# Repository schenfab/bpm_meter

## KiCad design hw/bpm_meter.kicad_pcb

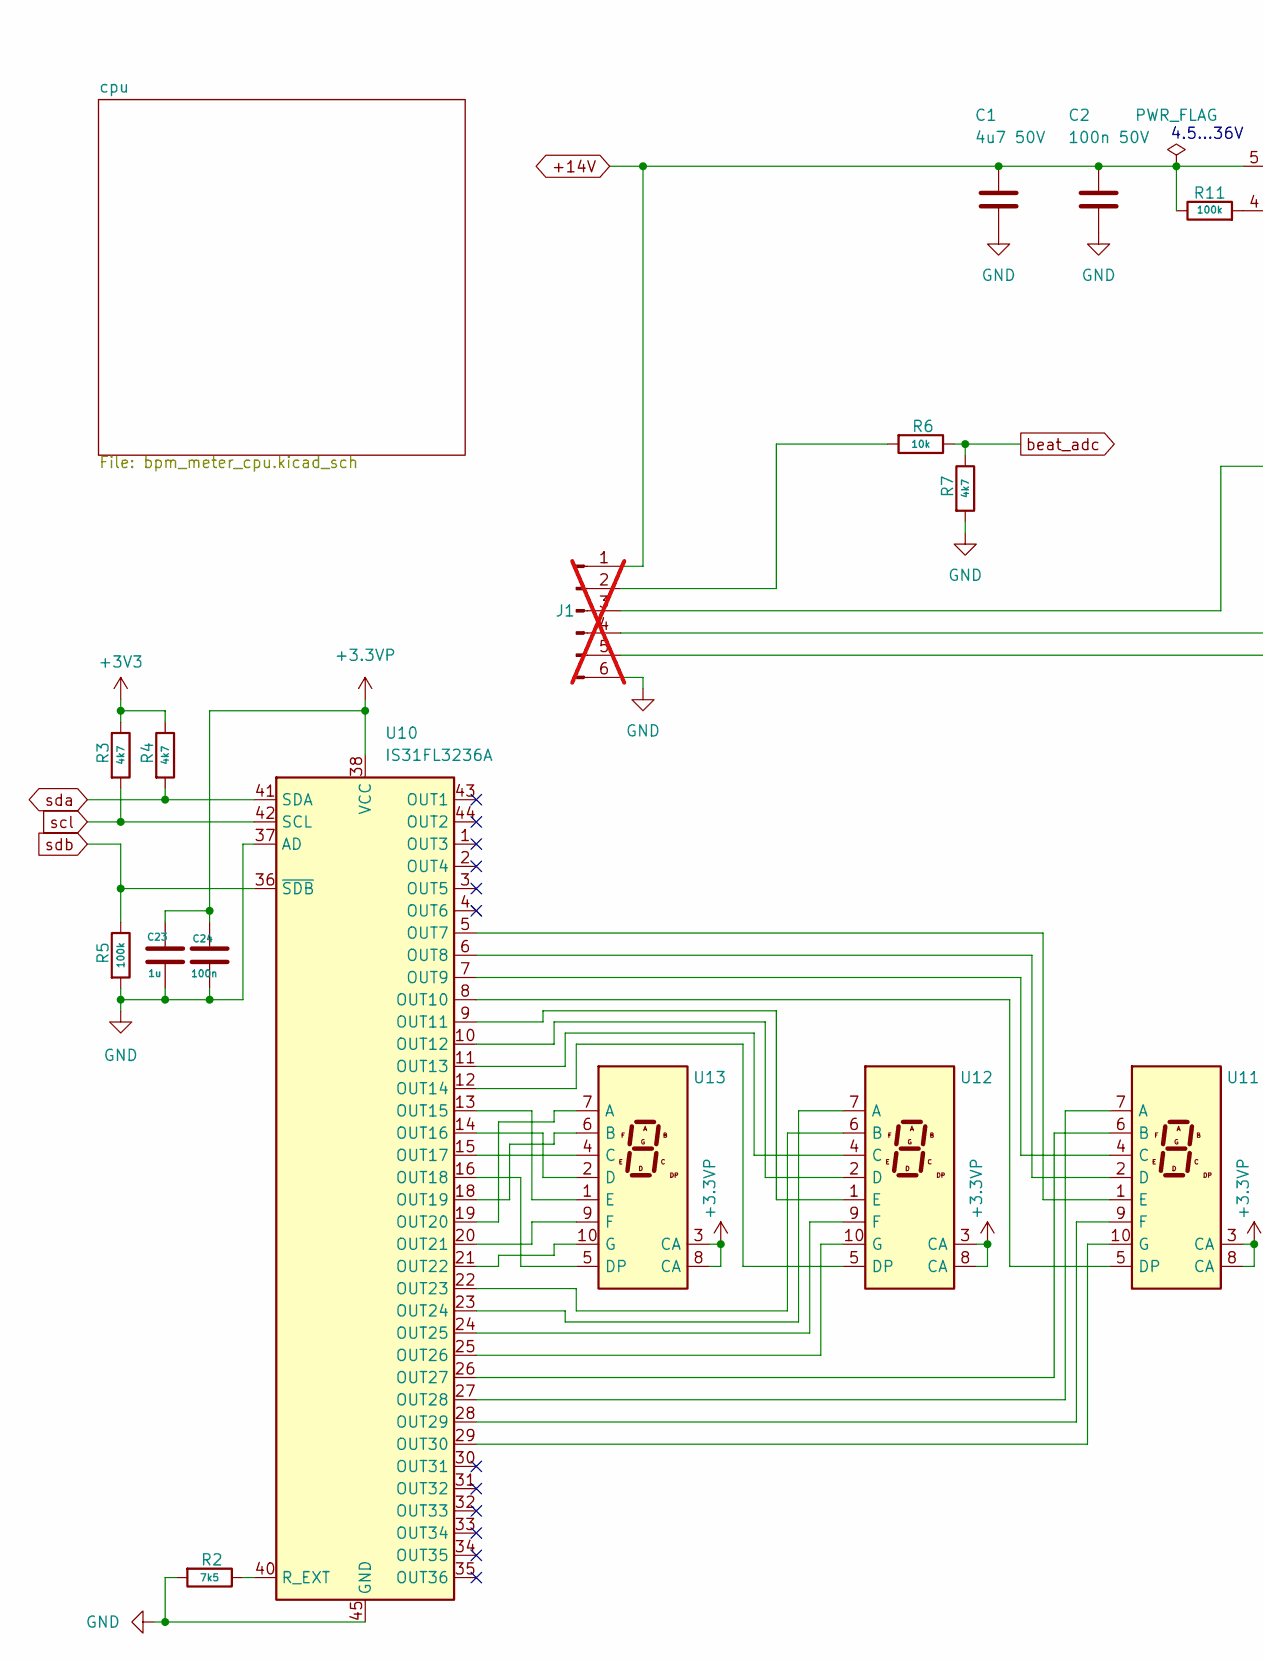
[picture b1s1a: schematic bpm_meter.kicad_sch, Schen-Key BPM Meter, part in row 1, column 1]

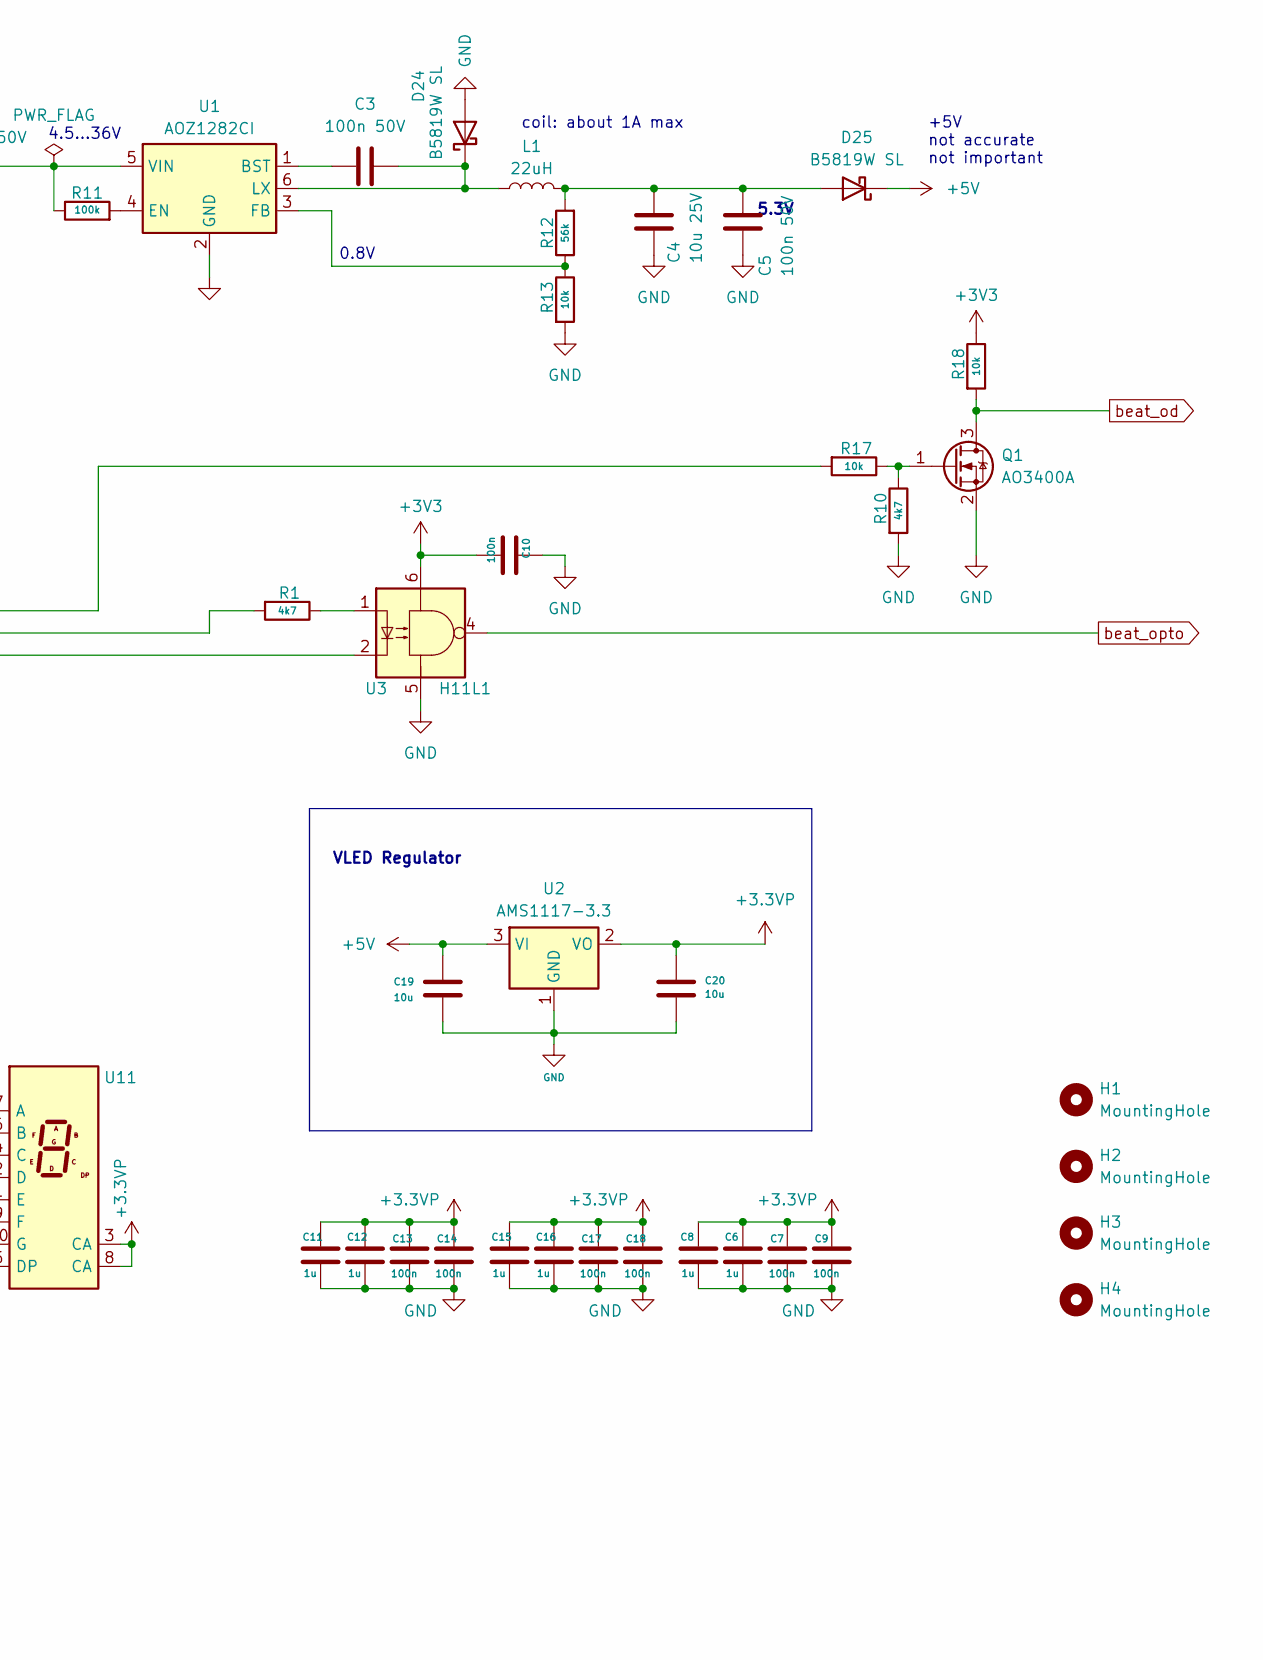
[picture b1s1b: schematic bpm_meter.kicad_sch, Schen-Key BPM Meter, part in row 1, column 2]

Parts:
C1: 4u7 50V; C_1210_3225Metric; JLC C515689
C2, C3, C5: 100n 50V; D_0805_2012Metric; JLC C49678
C4: 10u 25V; D_0805_2012Metric; JLC C15850
C6, C8, C11, C12, C15, C16, C23: 1u; C_0402_1005Metric_Pad0.74x0.62mm_HandSolder
C7, C9, C10, C13, C14, C17, C18, C24: 100n; C_0402_1005Metric_Pad0.74x0.62mm_HandSolder
C19, C20: 10u; C_0603_1608Metric
D24, D25: B5819W SL; D_SOD-123; JLC C8598
H1, H2, H3, H4: MountingHole; MountingHole_2.7mm_M2.5
J1: Conn_01x06_Pin; PinHeader_1x06_P2.54mm_Vertical; not fitted
L1: 22uH; L_MODBUS; JLC C5289423
Q1: AO3400A; SOT-23; JLC C20917
R1, R3, R4, R7, R10: 4k7; R_0402_1005Metric_Pad0.72x0.64mm_HandSolder
R2: 7k5; R_0402_1005Metric_Pad0.72x0.64mm_HandSolder
R5, R11: 100k; R_0402_1005Metric_Pad0.72x0.64mm_HandSolder
R6, R13, R17, R18: 10k; R_0402_1005Metric_Pad0.72x0.64mm_HandSolder
R12: 56k; R_0402_1005Metric_Pad0.72x0.64mm_HandSolder
U1: AOZ1282CI; SOT-23-6; JLC C111916
U2: AMS1117-3.3; SOT-223-3_TabPin2; JLC C6186
U3: H11L1; SOP-6-2.54mm; JLC C78589
U10: IS31FL3236A; QFN-44-5x5mm_P0.4mm; JLC C246443
U11, U12, U13: SLS0391FR1A1GD; SLS0391; JLC C2913076

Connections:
+3.3VP: C6.1, C7.1, C8.1, C9.1, C11.1, C12.1, C13.1, C14.1, C15.1, C16.1, C17.1, C18.1, C20.1, C23.1, C24.1, U2.2 (VO), U10.38 (VCC), U11.3 (CA), U11.8 (CA), U12.3 (CA), U12.8 (CA), U13.3 (CA), U13.8 (CA)
+3V3: C10.2, R3.1, R4.1, R18.1, U3.6; also elsewhere on the board
+5V: C19.1, D25.1 (K), U2.3 (VI); also elsewhere on the board
+14V: C1.1, C2.1, J1.1, R11.1, U1.5 (VIN)
GND: C1.2, C2.2, C4.1, C5.1, C6.2, C7.2, C8.2, C9.2, C10.1, C11.2, C12.2, C13.2, C14.2, C15.2, C16.2, C17.2, C18.2, C19.2, C20.2, C23.2, C24.2, D24.2 (A), J1.6, Q1.2 (S), R2.2, R5.2, R7.2, R10.2, R13.2, U1.2 (GND), U2.1 (GND), U3.5, U10.17 (GND), U10.37 (AD), U10.39 (GND), U10.45 (GND); also elsewhere on the board
unnamed: C3.2, D24.1 (K), L1.1, U1.6 (LX)
unnamed: C4.2, C5.2, D25.2 (A), L1.2, R12.2
unnamed: J1.2, R6.2
unnamed: J1.3, R17.2
unnamed: J1.4, R1.2
unnamed: J1.5, U3.2
unnamed: Q1.1 (G), R10.1, R17.1
unnamed: R1.1, U3.1
unnamed: C3.1, U1.1 (BST)
unnamed: R11.2, U1.4 (EN)
unnamed: R12.1, R13.1, U1.3 (FB)
unnamed: U10.5 (OUT7), U11.1 (E)
unnamed: U10.6 (OUT8), U11.2 (D)
unnamed: U10.7 (OUT9), U11.4 (C)
unnamed: U10.8 (OUT10), U11.5 (DP)
unnamed: U10.9 (OUT11), U12.1 (E)
unnamed: U10.10 (OUT12), U12.2 (D)
unnamed: U10.11 (OUT13), U12.4 (C)
unnamed: U10.12 (OUT14), U12.5 (DP)
unnamed: U10.13 (OUT15), U13.1 (E)
unnamed: U10.14 (OUT16), U13.2 (D)
unnamed: U10.15 (OUT17), U13.4 (C)
unnamed: U10.16 (OUT18), U13.5 (DP)
unnamed: U10.18 (OUT19), U13.6 (B)
unnamed: U10.19 (OUT20), U13.7 (A)
unnamed: U10.20 (OUT21), U13.9 (F)
unnamed: U10.21 (OUT22), U13.10 (G)
unnamed: U10.22 (OUT23), U12.6 (B)
unnamed: U10.23 (OUT24), U12.7 (A)
unnamed: U10.24 (OUT25), U12.9 (F)
unnamed: U10.25 (OUT26), U12.10 (G)
unnamed: U10.26 (OUT27), U11.6 (B)
unnamed: U10.27 (OUT28), U11.7 (A)
unnamed: U10.28 (OUT29), U11.9 (F)
unnamed: U10.29 (OUT30), U11.10 (G)
unnamed: R2.1, U10.40 (R_EXT)
beat_adc: R6.1, R7.1; also elsewhere on the board
beat_od: Q1.3 (D), R18.2; also elsewhere on the board
beat_opto: U3.4; also elsewhere on the board
scl: R3.2, U10.42 (SCL); also elsewhere on the board
sda: R4.2, U10.41 (SDA); also elsewhere on the board
sdb: R5.1, U10.36 (~SDB); also elsewhere on the board

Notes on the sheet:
+5V not accurate not important
coil: about 1A max
5.3V
VLED Regulator
4.5...36V
0.8V

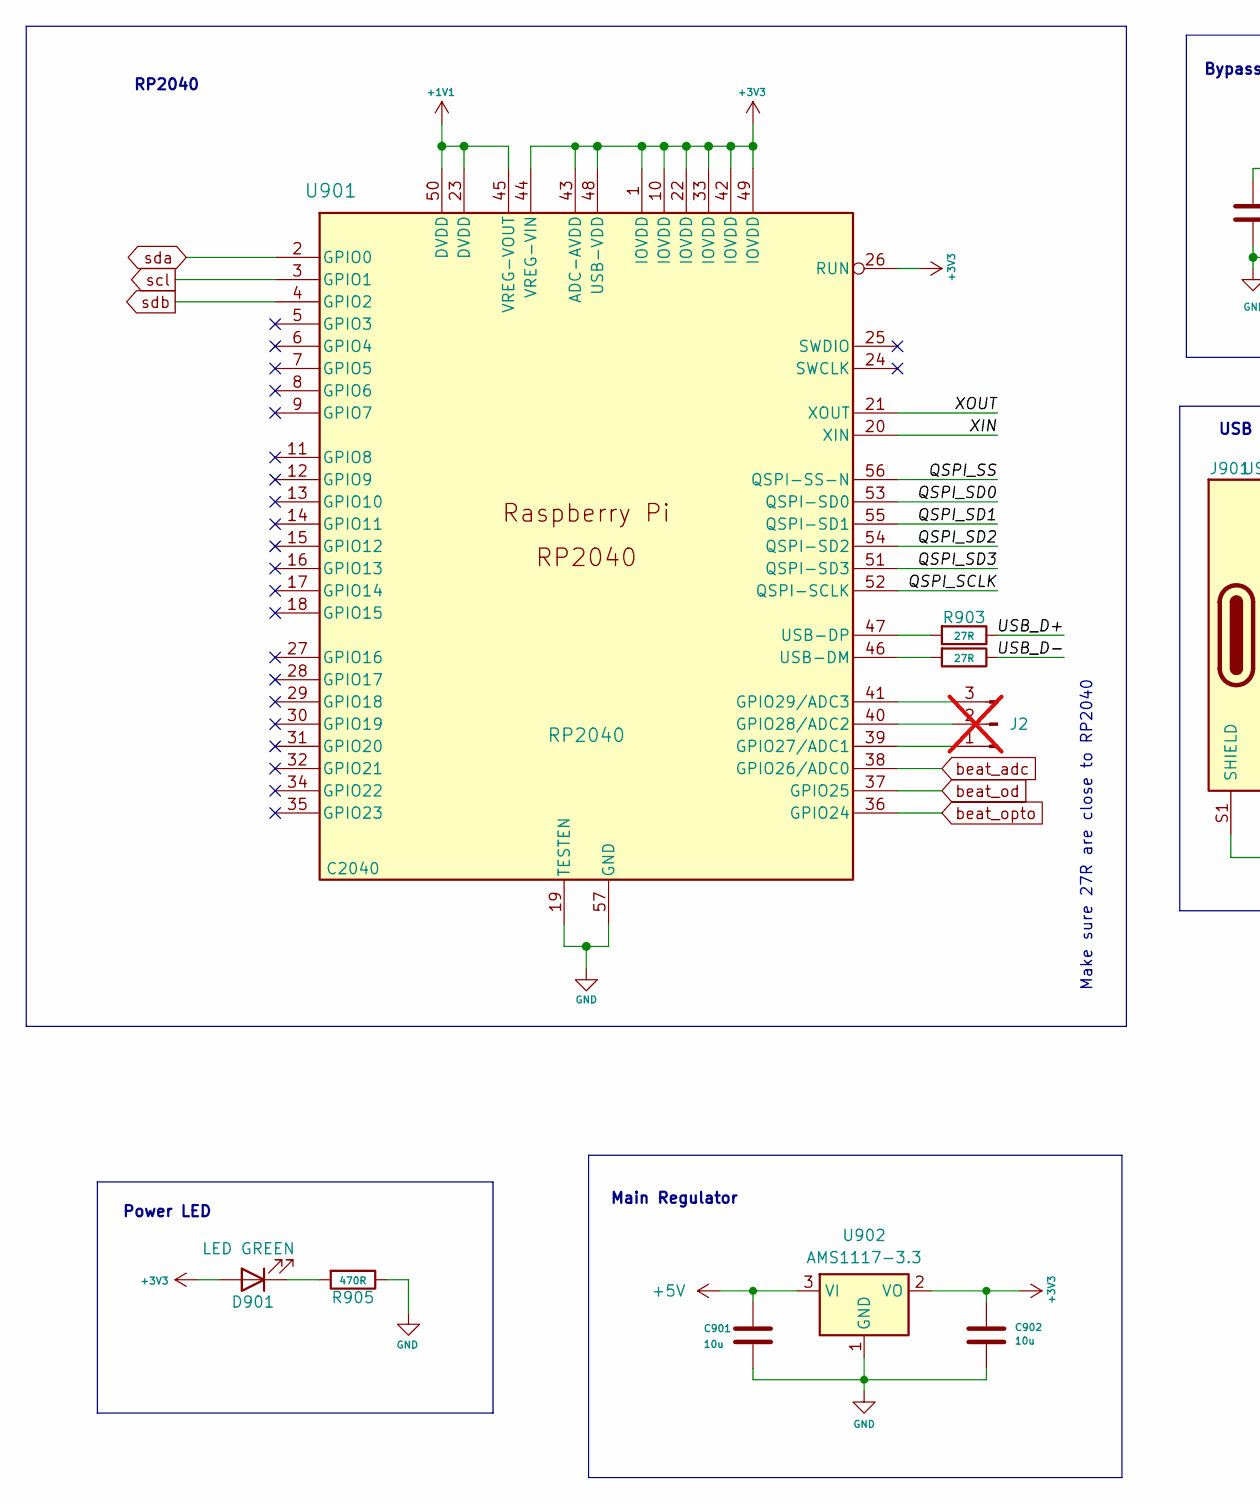
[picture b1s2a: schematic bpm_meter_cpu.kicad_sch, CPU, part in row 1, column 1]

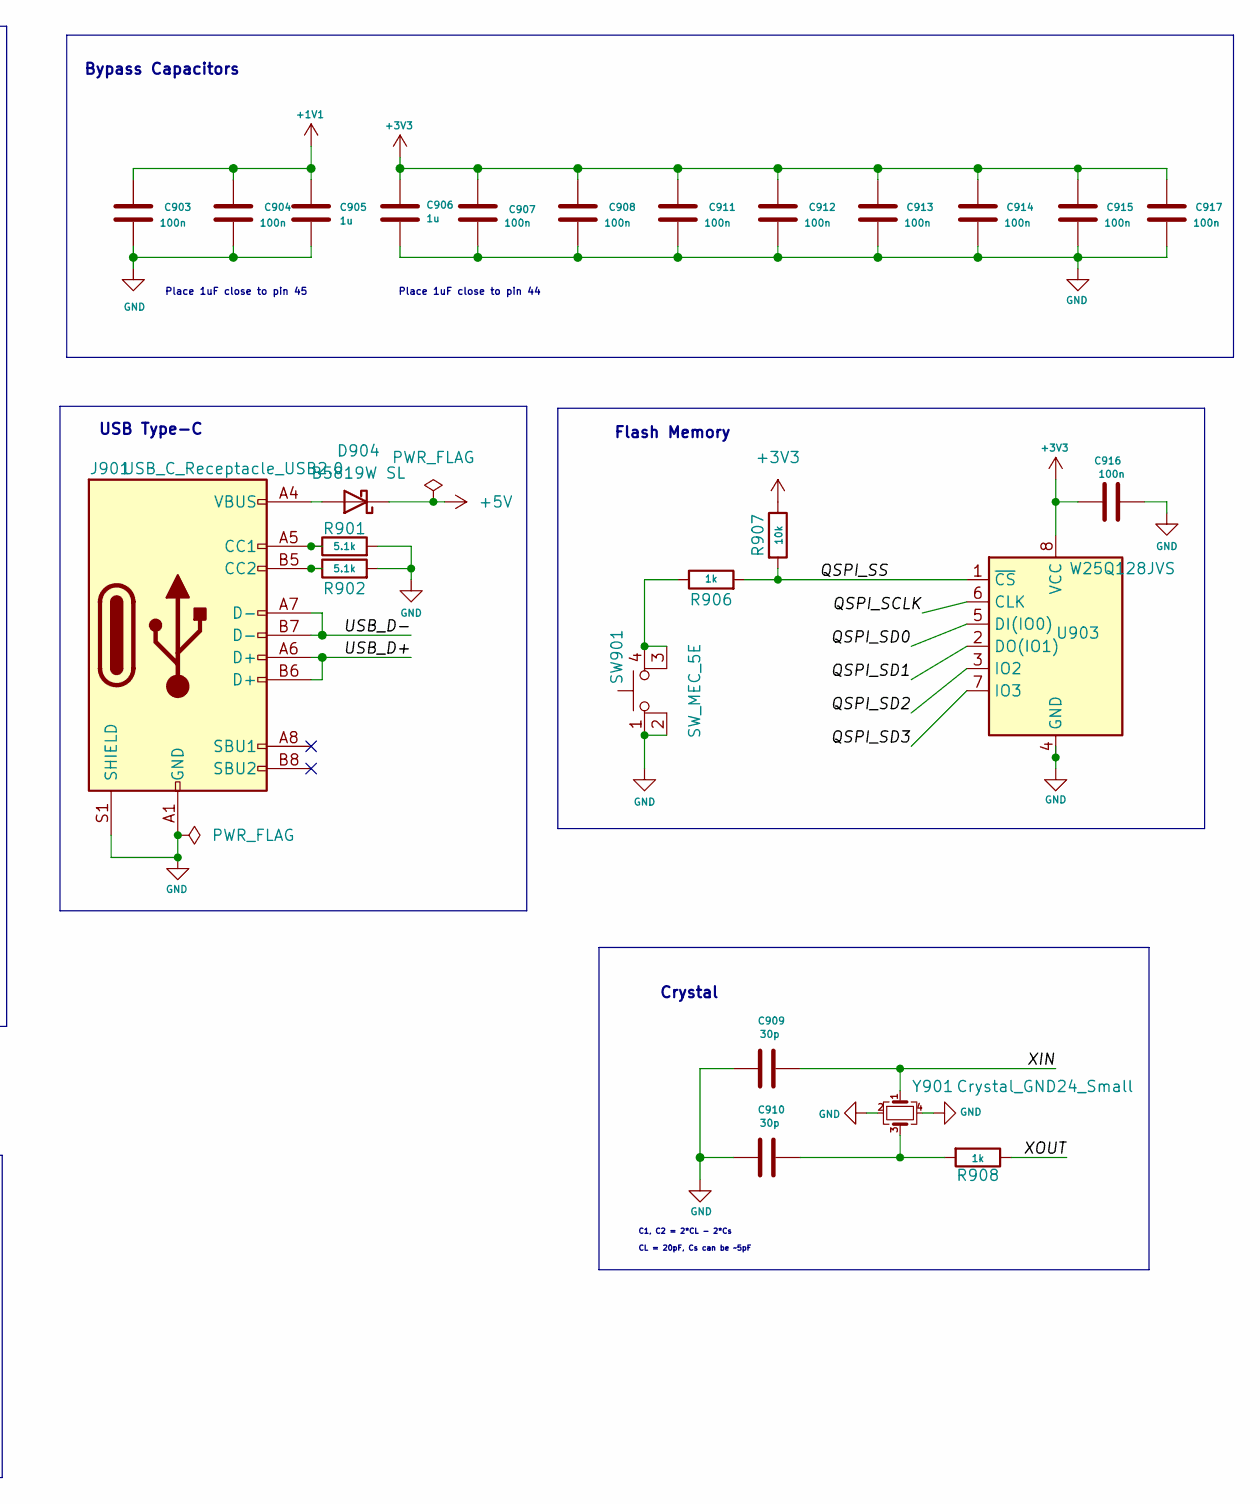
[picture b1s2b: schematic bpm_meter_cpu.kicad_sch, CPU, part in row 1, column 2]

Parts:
C901, C902: 10u; C_0603_1608Metric
C903, C904, C907, C908, C911, C912, C913, C914, C915, C916, C917: 100n; C_0402_1005Metric_Pad0.74x0.62mm_HandSolder
C905, C906: 1u; C_0402_1005Metric_Pad0.74x0.62mm_HandSolder
C909, C910: 30p; C_0402_1005Metric; JLC C1570
D901: LED GREEN; LED_0805_2012Metric; JLC C2297
D904: B5819W SL; D_SOD-123; JLC C8598
J2: Conn_01x03_Pin; PinHeader_1x03_P2.54mm_Vertical; not fitted
J901: USB_C_Receptacle_USB2.0; USB_C_Receptacle_Palconn_UTC16-G; JLC C165948
R901, R902: 5.1k; R_0402_1005Metric_Pad0.72x0.64mm_HandSolder
R903, R904: 27R; R_0402_1005Metric_Pad0.72x0.64mm_HandSolder
R905: 470R; R_0402_1005Metric_Pad0.72x0.64mm_HandSolder
R906, R908: 1k; R_0402_1005Metric_Pad0.72x0.64mm_HandSolder
R907: 10k; R_0402_1005Metric_Pad0.72x0.64mm_HandSolder
SW901: SW_MEC_5E; SW_TS-1187A-B-A-B; JLC C318884
U901: RP2040; RP2040-QFN-56; JLC C2040
U902: AMS1117-3.3; SOT-223-3_TabPin2; JLC C6186
U903: W25Q128JVS; SOIC-8_5.23x5.23mm_P1.27mm; JLC C97521
Y901: Crystal_GND24_Small; Crystal_SMD_3225-4Pin_3.2x2.5mm; JLC C9002

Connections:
+1V1: C903.1, C904.1, C905.1, U901.23 (DVDD), U901.45 (VREG-VOUT), U901.50 (DVDD)
+3V3: C902.1, C906.1, C907.1, C908.1, C911.1, C912.1, C913.1, C914.1, C915.1, C916.1, C917.1, D901.2 (A), R907.1, U901.1 (IOVDD), U901.10 (IOVDD), U901.22 (IOVDD), U901.26 (RUN), U901.33 (IOVDD), U901.42 (IOVDD), U901.43 (ADC-AVDD), U901.44 (VREG-VIN), U901.48 (USB-VDD), U901.49 (IOVDD), U902.2 (VO), U903.8 (VCC); also elsewhere on the board
+5V: C901.1, D904.1 (K), U902.3 (VI); also elsewhere on the board
/cpu/QSPI_SCLK: U901.52 (QSPI-SCLK), U903.6 (CLK)
/cpu/QSPI_SD0: U901.53 (QSPI-SD0), U903.5 (DI(IO0))
/cpu/QSPI_SD1: U901.55 (QSPI-SD1), U903.2 (DO(IO1))
/cpu/QSPI_SD2: U901.54 (QSPI-SD2), U903.3 (IO2)
/cpu/QSPI_SD3: U901.51 (QSPI-SD3), U903.7 (IO3)
/cpu/QSPI_SS: R906.2, R907.2, U901.56 (QSPI-SS-N), U903.1 (~CS)
/cpu/USB_D+: J901.A6 (D+), J901.B6 (D+), R903.1
/cpu/USB_D-: J901.A7 (D-), J901.B7 (D-), R904.1
/cpu/XIN: C909.1, U901.20 (XIN), Y901.1
/cpu/XOUT: R908.1, U901.21 (XOUT)
GND: C901.2, C902.2, C903.2, C904.2, C905.2, C906.2, C907.2, C908.2, C909.2, C910.2, C911.2, C912.2, C913.2, C914.2, C915.2, C916.2, C917.2, J901.A1 (GND), J901.A12 (GND), J901.B1 (GND), J901.B12 (GND), J901.S1 (SHIELD), R901.2, R902.2, R905.1, SW901.1, SW901.2, U901.19 (TESTEN), U901.57 (GND), U902.1 (GND), U903.4 (GND), Y901.2, Y901.4; also elsewhere on the board
unnamed: C910.1, R908.2, Y901.3
unnamed: D901.1 (K), R905.2
unnamed: D904.2 (A), J901.A4 (VBUS), J901.A9 (VBUS), J901.B4 (VBUS), J901.B9 (VBUS)
unnamed: J2.1, U901.39 (GPIO27/ADC1)
unnamed: J2.2, U901.40 (GPIO28/ADC2)
unnamed: J2.3, U901.41 (GPIO29/ADC3)
unnamed: J901.A5 (CC1), R901.1
unnamed: J901.B5 (CC2), R902.1
unnamed: R906.1, SW901.3 (K), SW901.4 (A)
unnamed: R904.2, U901.46 (USB-DM)
unnamed: R903.2, U901.47 (USB-DP)
beat_adc: U901.38 (GPIO26/ADC0); also elsewhere on the board
beat_od: U901.37 (GPIO25); also elsewhere on the board
beat_opto: U901.36 (GPIO24); also elsewhere on the board
scl: U901.3 (GPIO1); also elsewhere on the board
sda: U901.2 (GPIO0); also elsewhere on the board
sdb: U901.4 (GPIO2); also elsewhere on the board

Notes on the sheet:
USB Type-C
Crystal
Make sure 27R are close to RP2040
RP2040
Place 1uF close to pin 44
Place 1uF close to pin 45
Power LED
Main Regulator
Flash Memory
Bypass Capacitors
C1, C2 = 2*CL - 2*Cs CL = 20pF, Cs can be ~5pF

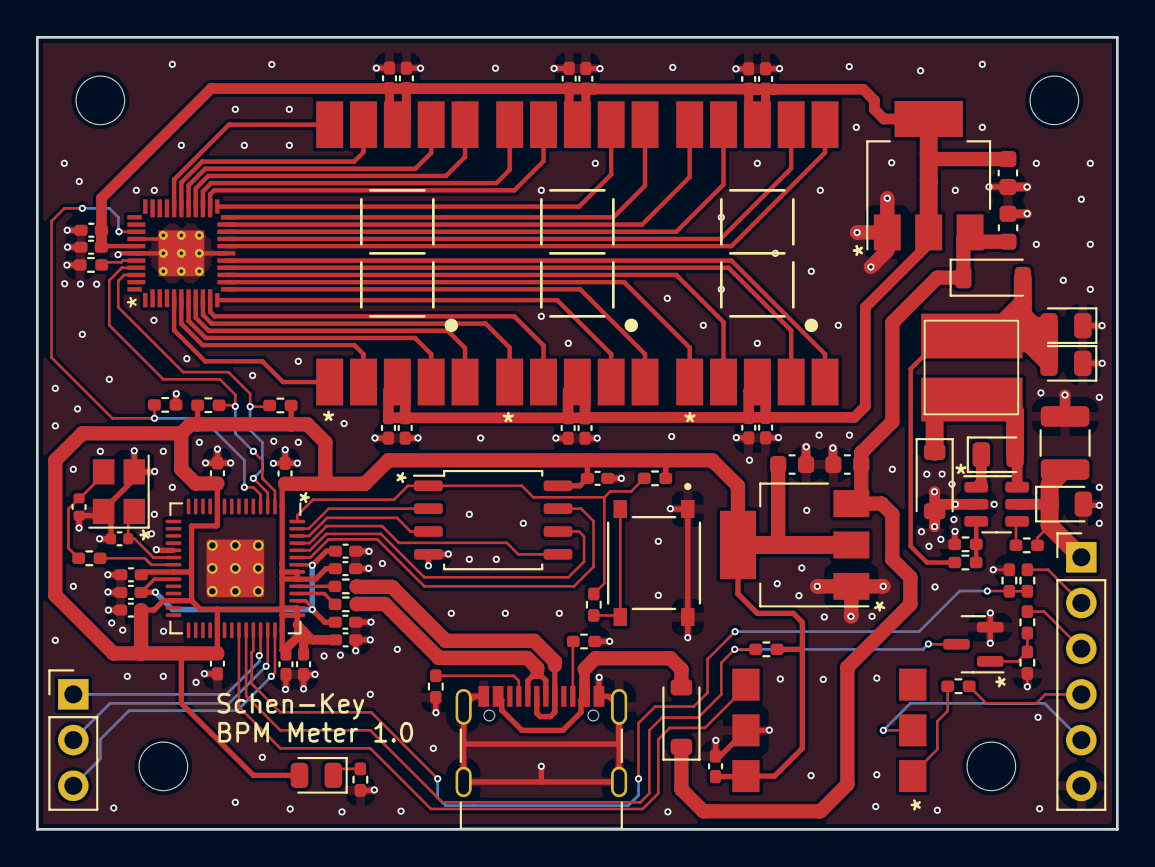
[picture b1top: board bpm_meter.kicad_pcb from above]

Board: 2 copper layers, 60.0 x 44.0 mm, 85 parts (0 on the bottom side), 69 nets.

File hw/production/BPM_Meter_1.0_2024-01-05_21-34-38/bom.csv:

Designator,Footprint,Quantity,Value,LCSC Part #
C1,1210,1,4u7 50V,C515689
"C10, C13, C14, C17, C18, C24, C7, C9, C903, C904, C907, C908, C911, C912, C913, C914, C915, C916, C917",0402,19,100n,
"C11, C12, C15, C16, C23, C6, C8, C905, C906",0402,9,1u,
"C19, C20, C901, C902",0603,4,10u,
"C2, C3, C5",0805,3,100n 50V,C49678
C4,0805,1,10u 25V,C15850
"C909, C910",0402,2,30p,C1570
"D24, D25, D904",D_SOD-123,3,B5819W SL,C8598
D901,0805,1,LED GREEN,C2297
"H1, H2, H3, H4",MountingHole_2.7mm_M2.5,4,MountingHole,
J901,USB_C_Receptacle_Palconn_UTC16-G,1,USB_C_Receptacle_USB2.0,C165948
L1,L_MODBUS,1,22uH,C5289423
Q1,SOT-23,1,AO3400A,C20917
"R1, R10, R3, R4, R7",0402,5,4k7,
"R11, R5",0402,2,100k,
R12,0402,1,56k,
"R13, R17, R18, R6, R907",0402,5,10k,
R2,0402,1,7k5,
"R901, R902",0402,2,5.1k,
"R903, R904",0402,2,27R,
R905,0402,1,470R,
"R906, R908",0402,2,1k,
SW901,SW_TS-1187A-B-A-B,1,SW_MEC_5E,C318884
U1,SOT-23-6,1,AOZ1282CI,C111916
U10,QFN-44-5x5mm_P0.4mm,1,IS31FL3236A,C246443
"U11, U12, U13",SLS0391,3,SLS0391FR1A1GD,C2913076
"U2, U902",SOT-223-3_TabPin2,2,AMS1117-3.3,C6186
U3,SOP-6-2.54mm,1,H11L1,C78589
U901,RP2040-QFN-56,1,RP2040,C2040
U903,SOIC-8_5.23x5.23mm_P1.27mm,1,W25Q128JVS,C97521
Y901,Crystal_SMD_3225-4Pin_3.2x2.5mm,1,Crystal_GND24_Small,C9002

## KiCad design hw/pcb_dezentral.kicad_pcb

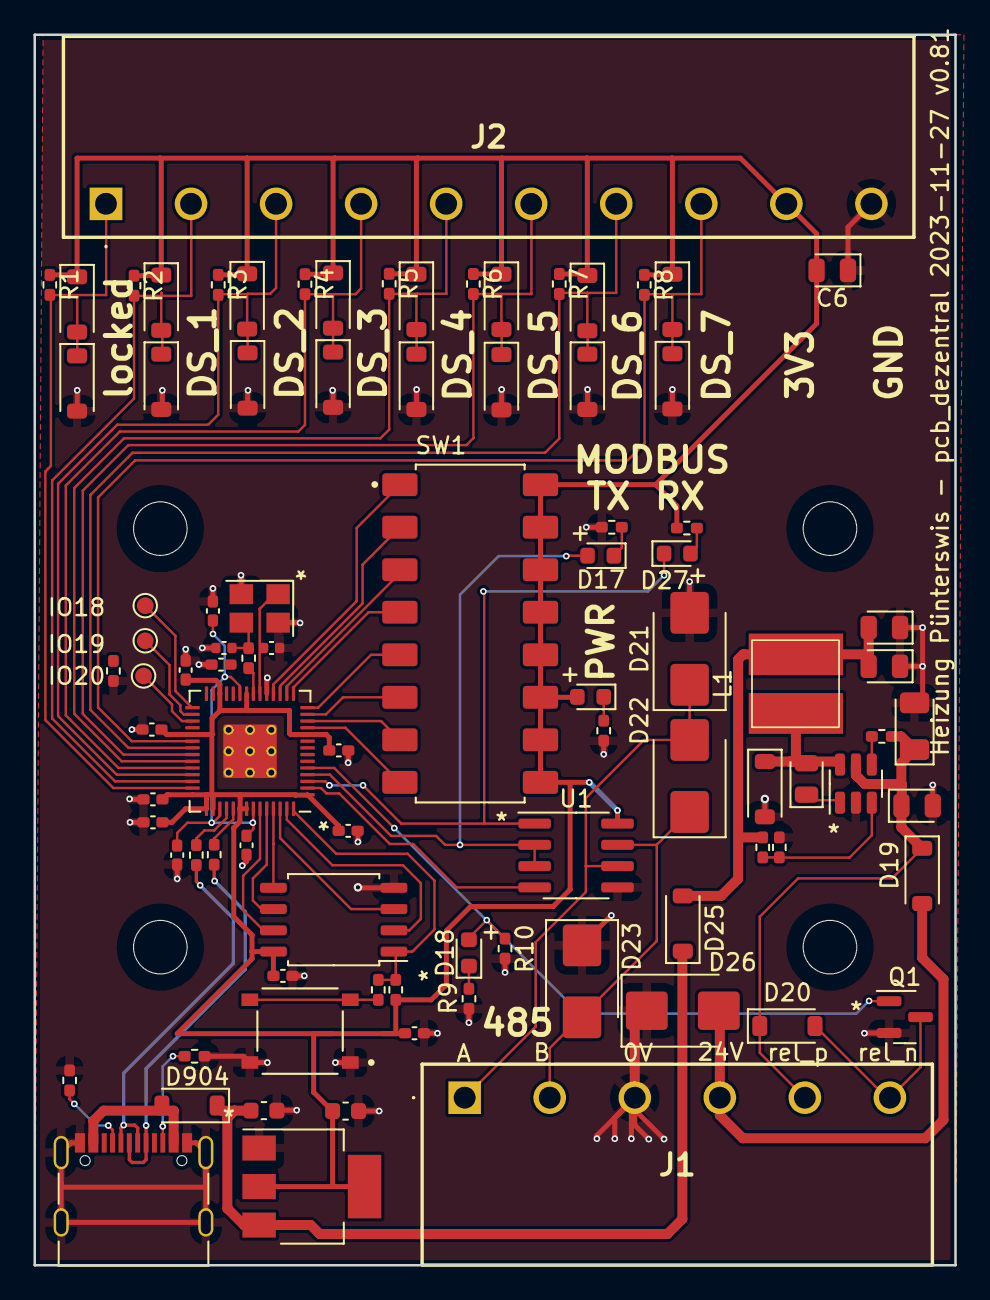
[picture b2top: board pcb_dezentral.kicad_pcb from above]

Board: 2 copper layers, 55.0 x 73.5 mm, 92 parts (0 on the bottom side), 58 nets.

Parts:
C1: 4u7 50V; D_1206_3216Metric
C2, C3, C5, C6: 100n 50V; D_0805_2012Metric
C4: 10u 25V; D_0805_2012Metric
C901, C902: 10u; C_0603_1608Metric
C903, C904, C907, C908, C911, C912, C913, C914, C915, C916: 100n; C_0402_1005Metric_Pad0.74x0.62mm_HandSolder
C905, C906: 1u; C_0402_1005Metric_Pad0.74x0.62mm_HandSolder
C909, C910: 30p; C_0402_1005Metric
D1, D2, D3, D4, D5, D6, D7, D8, D9, D10, D11, D12, D13, D14, D15, D16, D19, D20, D24, D25, D904: B5819W SL; D_SOD-123
D17: LED RED; LED_0603_1608Metric
D18: LED WHITE; LED_0603_1608Metric
D21, D22, D23: SMBJ6.5CA; D_SMB
D26: SMBJ30CA; D_SMB
D27: LED BLUE; LED_0603_1608Metric
D901: LED GREEN; LED_0603_1608Metric
HOLDER1: din_rail_pcb_holder
IO18, IO19, IO20: TestPoint; TestPoint_Pad_D1.0mm
J1: weidmueller_SL5.08HC-06-90
J2: weidmueller_SL5.08HC-10-90
J901: USB_C_Receptacle_USB2.0; USB_C_Receptacle_Palconn_UTC16-G
L1: 22uH; L_MODBUS
Q1: AO3400A; SOT-23
R1, R2, R3, R4, R5, R6, R7, R8, R14: 4k7; R_0402_1005Metric_Pad0.72x0.64mm_HandSolder
R9: 470; R_0402_1005Metric_Pad0.72x0.64mm_HandSolder
R10, R13: 10k; R_0402_1005Metric_Pad0.72x0.64mm_HandSolder
R11: 100k; R_0402_1005Metric_Pad0.72x0.64mm_HandSolder
R12: 56k; R_0402_1005Metric_Pad0.72x0.64mm_HandSolder
R15, R16, R905: 470R; R_0402_1005Metric_Pad0.72x0.64mm_HandSolder
R901, R902: 5.1K; R_0402_1005Metric_Pad0.72x0.64mm_HandSolder
R903, R904: 27R; R_0402_1005Metric_Pad0.72x0.64mm_HandSolder
R906: 1K; R_0402_1005Metric_Pad0.72x0.64mm_HandSolder
R907: 10K; R_0402_1005Metric_Pad0.72x0.64mm_HandSolder
R908: 1k; R_0402_1005Metric_Pad0.72x0.64mm_HandSolder
SW1: dip_switch_SPST16
SW901: SW_MEC_5E; SW_TS-1187A-B-A-B
U1: SP3485EN-L/TR; SOIC-8_3.9x4.9mm_P1.27mm
U2: AOZ1282CI; SOT-23-6
U901: RP2040; RP2040-QFN-56
U902: AMS1117-3.3; SOT-223-3_TabPin2
U903: W25Q128JVS; SOIC-8_5.23x5.23mm_P1.27mm
Y901: Crystal_GND24_Small; Crystal_SMD_3225-4Pin_3.2x2.5mm

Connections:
24Vp: C1.1, C2.1, D19.1 (K), D20.1 (K), J1.5, R11.1, U2.5 (VIN)
485_24V: D19.2 (A), D26.2 (A2), J1.4
485_A: D21.1 (A1), D22.2 (A2), J1.1, U1.6 (A)
485_B: D22.1 (A1), D23.2 (A2), J1.2, U1.7 (B)
+1V1: C903.1, C904.1, C905.1, U901.23 (DVDD), U901.45 (VREG-VOUT), U901.50 (DVDD)
+3V3: C6.2, C902.1, C906.1, C907.1, C908.1, C911.1, C912.1, C913.1, C914.1, C915.1, C916.1, D1.1 (K), D3.1 (K), D5.1 (K), D7.1 (K), D9.1 (K), D11.1 (K), D13.1 (K), D15.1 (K), D901.2 (A), J2.9, R1.1, R2.1, R3.1, R4.1, R5.1, R6.1, R7.1, R8.1, R15.1, R907.1, SW1.1-1, SW1.2-1, SW1.3-1, SW1.4-1, SW1.5-1, SW1.6-1, SW1.7-1, SW1.8-1, U1.8 (VCC), U901.1 (IOVDD), U901.10 (IOVDD), U901.22 (IOVDD), U901.26 (RUN), U901.33 (IOVDD), U901.42 (IOVDD), U901.43 (ADC-AVDD), U901.44 (VREG-VIN), U901.48 (USB-VDD), U901.49 (IOVDD), U902.2 (VO), U903.8 (VCC)
+5V: C901.1, D25.1 (K), D904.1 (K), U902.3 (VI)
/cpu/QSPI_SCLK: U901.52 (QSPI-SCLK), U903.6 (CLK)
/cpu/QSPI_SD0: U901.53 (QSPI-SD0), U903.5 (DI(IO0))
/cpu/QSPI_SD1: U901.55 (QSPI-SD1), U903.2 (DO(IO1))
/cpu/QSPI_SD2: U901.54 (QSPI-SD2), U903.3 (IO2)
/cpu/QSPI_SD3: U901.51 (QSPI-SD3), U903.7 (IO3)
/cpu/QSPI_SS: R906.2, R907.2, U901.56 (QSPI-SS-N), U903.1 (~CS)
/cpu/USB_D+: J901.A6 (D+), J901.B6 (D+), R903.1
/cpu/USB_D-: J901.A7 (D-), J901.B7 (D-), R904.1
/cpu/XIN: C909.1, U901.20 (XIN), Y901.1
/cpu/XOUT: R908.1, U901.21 (XOUT)
GND: C1.2, C2.2, C4.1, C5.1, C6.1, C901.2, C902.2, C903.2, C904.2, C905.2, C906.2, C907.2, C908.2, C909.2, C910.2, C911.2, C912.2, C913.2, C914.2, C915.2, C916.2, D2.2 (A), D4.2 (A), D6.2 (A), D8.2 (A), D10.2 (A), D12.2 (A), D14.2 (A), D16.2 (A), D21.2 (A2), D23.1 (A1), D24.2 (A), D26.1 (A1), J1.3, J2.10, J901.A1 (GND), J901.A12 (GND), J901.B1 (GND), J901.B12 (GND), J901.S1 (SHIELD), Q1.2 (S), R9.2, R10.2, R13.2, R14.2, R16.2, R901.2, R902.2, R905.1, SW901.1, SW901.2, U1.5 (GND), U2.2 (GND), U901.19 (TESTEN), U901.57 (GND), U902.1 (GND), U903.4 (GND), Y901.2, Y901.4
MODBUS_DE: D17.2 (A), R14.1, U1.2 (~RE), U1.3 (DE), U901.4 (GPIO2)
MODBUS_DI: U1.4 (DI), U901.2 (GPIO0)
MODBUS_RO: D27.1 (K), U1.1 (RO), U901.3 (GPIO1)
unnamed: C910.1, R908.2, Y901.3
unnamed: D17.1 (K), R16.1
unnamed: D18.1 (K), R9.1
unnamed: C3.2, D24.1 (K), L1.1, U2.6 (LX)
unnamed: C4.2, C5.2, D25.2 (A), L1.2, R12.2
unnamed: D27.2 (A), R15.2
unnamed: D901.1 (K), R905.2
unnamed: D904.2 (A), J901.A4 (VBUS), J901.A9 (VBUS), J901.B4 (VBUS), J901.B9 (VBUS)
unnamed: J901.A5 (CC1), R901.1
unnamed: J901.B5 (CC2), R902.1
unnamed: R906.1, SW901.3 (K), SW901.4 (A)
unnamed: C3.1, U2.1 (BST)
unnamed: R11.2, U2.4 (EN)
unnamed: R12.1, R13.1, U2.3 (FB)
unnamed: IO18.1, U901.29 (GPIO18)
unnamed: IO19.1, U901.30 (GPIO19)
unnamed: IO20.1, U901.31 (GPIO20)
unnamed: R904.2, U901.46 (USB-DM)
unnamed: R903.2, U901.47 (USB-DP)
ds_0: D1.2 (A), D2.1 (K), J2.1, R1.2, U901.41 (GPIO29/ADC3)
ds_1: D3.2 (A), D4.1 (K), J2.2, R2.2, U901.40 (GPIO28/ADC2)
ds_2: D5.2 (A), D6.1 (K), J2.3, R3.2, U901.39 (GPIO27/ADC1)
ds_3: D7.2 (A), D8.1 (K), J2.4, R4.2, U901.38 (GPIO26/ADC0)
ds_4: D9.2 (A), D10.1 (K), J2.5, R5.2, U901.37 (GPIO25)
ds_5: D11.2 (A), D12.1 (K), J2.6, R6.2, U901.36 (GPIO24)
ds_6: D13.2 (A), D14.1 (K), J2.7, R7.2, U901.35 (GPIO23)
ds_7: D15.2 (A), D16.1 (K), J2.8, R8.2, U901.34 (GPIO22)
modbus_addr_0: SW1.1, U901.18 (GPIO15)
modbus_addr_1: SW1.2, U901.17 (GPIO14)
modbus_addr_2: SW1.3, U901.16 (GPIO13)
modbus_addr_3: SW1.4, U901.15 (GPIO12)
modbus_addr_4: SW1.5, U901.14 (GPIO11)
modbus_addr_5: SW1.6, U901.13 (GPIO10)
modbus_addr_6: SW1.7, U901.12 (GPIO9)
modbus_addr_7: SW1.8, U901.11 (GPIO8)
rel: D18.2 (A), Q1.1 (G), R10.1, U901.5 (GPIO3)
rel_n: D20.2 (A), J1.6, Q1.3 (D)

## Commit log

2023-12-21 Cloned from puenterswis_heizung_2023_git
2023-12-21 Renamed the KiCad project
2023-12-21 Removed unused stuff and added beat input
2023-12-21 Added a 7-segment LED symbol
2023-12-23 Added the 10mm segment display to the library
2023-12-23 Added H11L1 optocoupler to library and schematic
2023-12-23 Connected the segment displays using dual FETs
2023-12-23 Export to PCB
2023-12-31 Now using LP5030 LED driver
2024-01-03 Changed LED driver to ISSI IS31FL3236A
2024-01-04 Replaced mechanical holder with four M2.5 mounting holes
2024-01-04 Removed unused tracks, did some prearrangement of components
2024-01-04 Optimized layout of the RP2040
2024-01-05 Fixed the PCB outlines and placement of some components
2024-01-05 Routed part of the design
2024-01-05 Routed the power supplies and beat inputs
2024-01-05 Routing almost finished, QSPI flash missing
2024-01-05 Finished routing all nets
2024-01-05 Minor optimizations
2024-01-05 Production variant v1
2024-01-14 Hardware v1.0 taped-out to JLCPCB on 06.01.2024
2024-01-14 Added stock MicroPython firmware for RP2040
2024-01-14 Added Python test code for LED printing
2024-01-14 Put the LED driver into a class
2024-01-15 The LED driver is now able to print dots, and has been moved to a separate module
2024-01-17 Started implementing a proper BPM display routine
2024-01-18 First working version
2024-01-18 Formatted the Python sources with black
2024-01-22 Added a blinking point to indicate that BPM was updated
2024-01-27 Changed the IRQ to falling edge since the beat inputs are inverted
2024-01-27 Added the required files to 3D-print a suitable case
2024-01-27 Added a fully permissive LICENSE
2024-01-28 Changed LED driver PWM frequency so the power supply ripple does not interfere with the audio signal

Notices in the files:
hw/pcb_dezentral.kicad_pcb:
Released under MIT Open-source License
parts and their libraries:
License: CC BY 4.0
